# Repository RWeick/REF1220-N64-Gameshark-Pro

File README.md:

# REF1220-N64-Gameshark-Pro
An optimized PCB for the N64 Gameshark Pro as well as the full schematic. This is the second revision of the N64 Gameshark which was intended to support a smart card method of updating codes and adding features. The Gameshark Pro bin file should be programmed with the low bytes to the bottom SST and the high bytes to the top SST. It's worth noting that no smart cards were ever released for use with this Gameshark.

PCB Thickness: 1.2 mm

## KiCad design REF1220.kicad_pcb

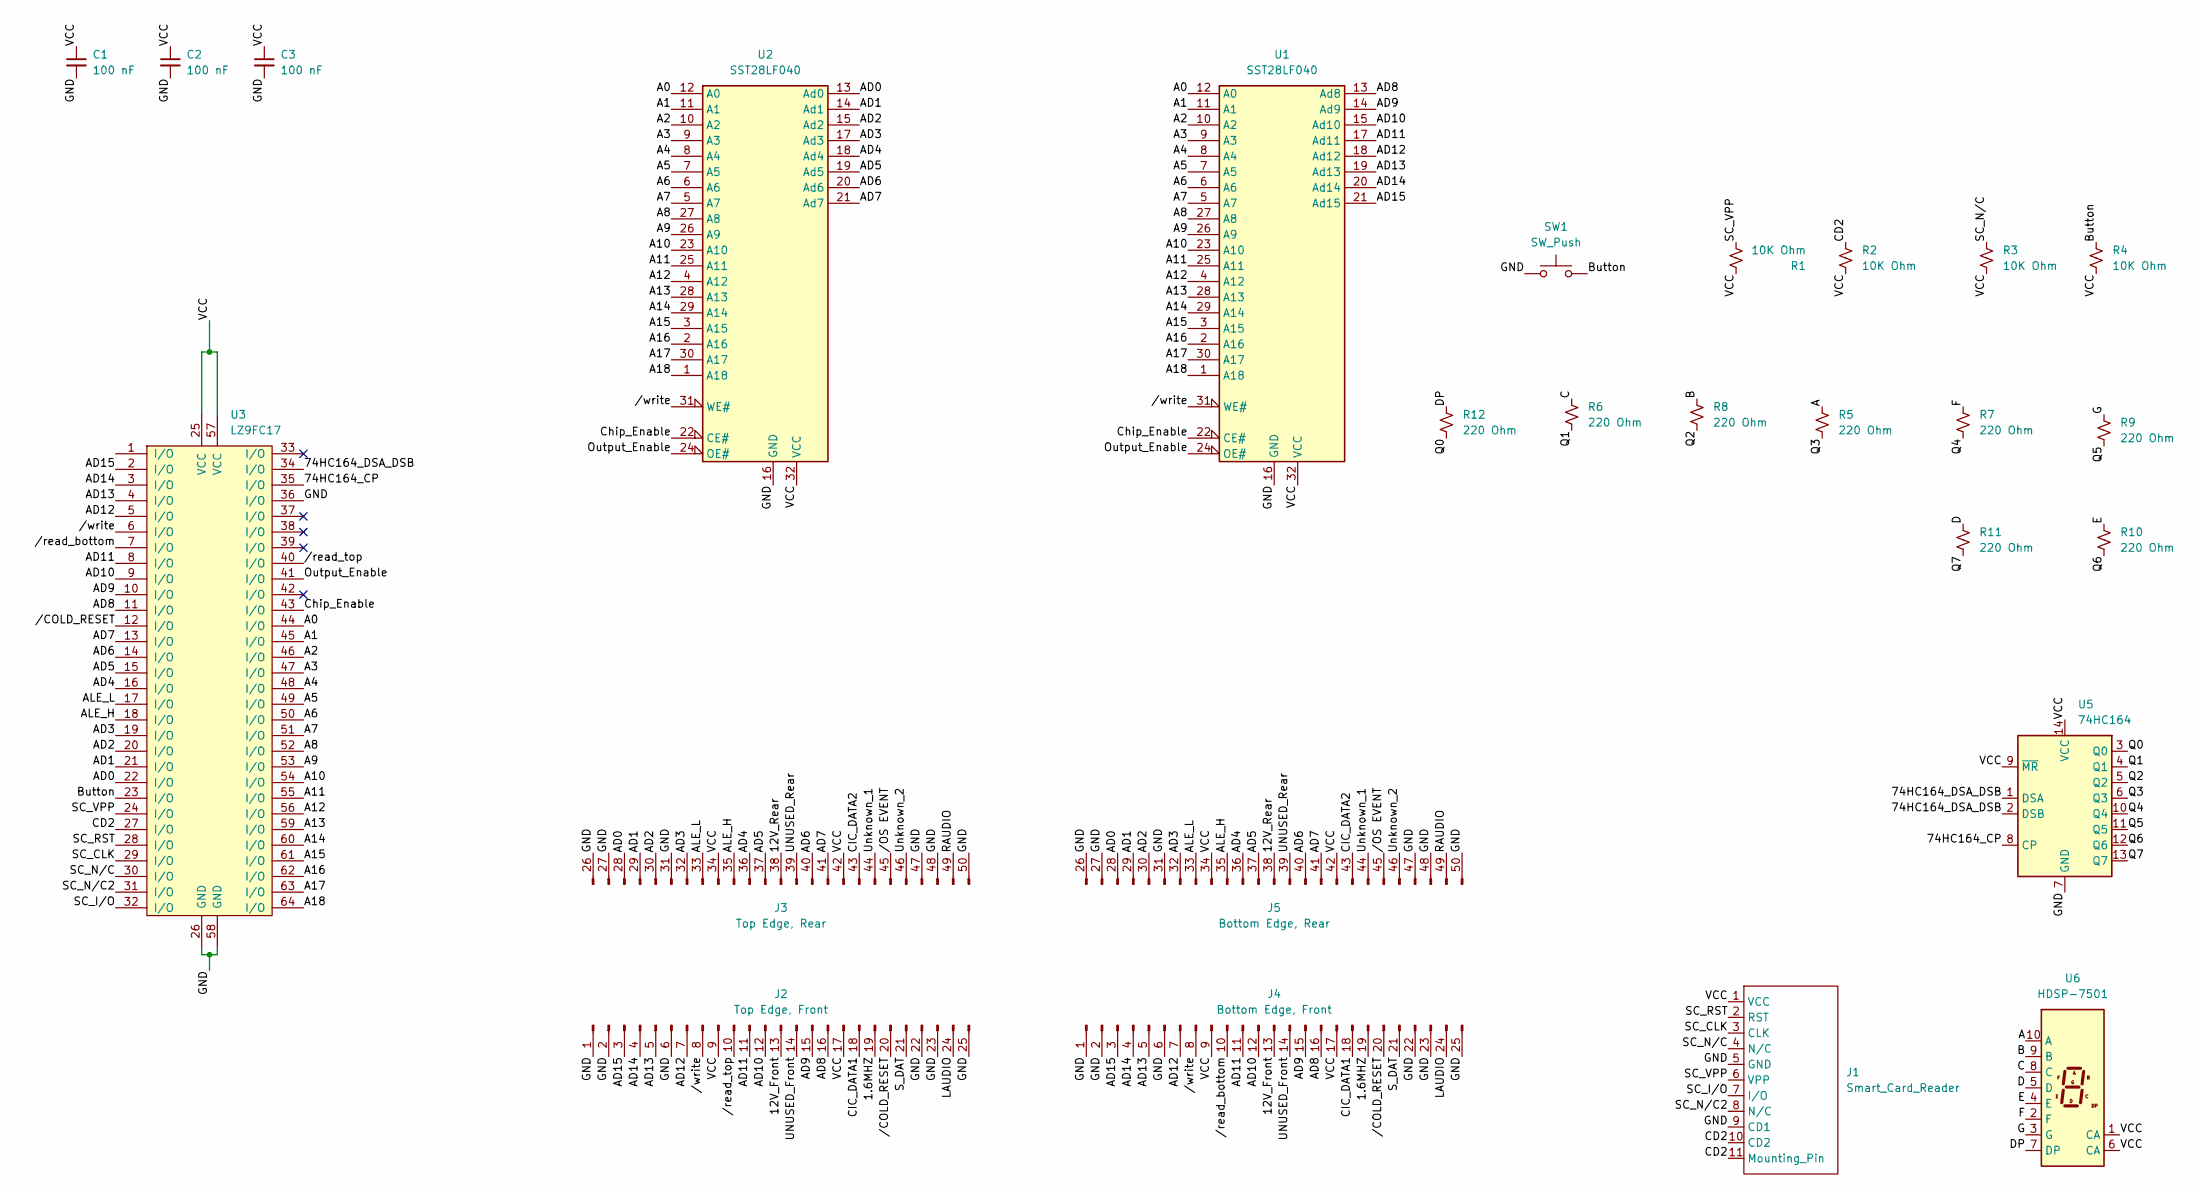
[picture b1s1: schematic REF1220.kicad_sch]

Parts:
C1, C2, C3: 100 nF; 100 nF Cap
J1: Smart_Card_Reader; Smart Card
J2: Top Edge, Front; Cart Edge Connector
J3: Top Edge, Rear; Cart Edge Connector Back
J4: Bottom Edge, Front; Cart Edge Connector
J5: Bottom Edge, Rear; Cart Edge Connector Back
R1, R2, R3, R4: 10K Ohm; 10k Ohm Resistor
R5, R6, R7, R8, R9, R10, R11, R12: 220 Ohm; 220 Ohm Resistor
SW1: SW_Push; 1mm Push Button
U1, U2: SST28LF040; PLCC32
U3: LZ9FC17; LZ9FC17 GAL
U5: 74HC164
U6: HDSP-7501; HDSP-7401

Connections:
/1.6MHZ: J2.19, J4.19
/12V_Front: J2.13, J4.13
/12V_Rear: J3.38 (Pin_13), J5.38 (Pin_13)
/74HC164_CP: U3.35 (I/O), U5.8 (CP)
/74HC164_DSA_DSB: U3.34 (I/O), U5.1 (DSA), U5.2 (DSB)
/A: R5.1, U6.10 (A)
/A0: U1.12 (A0), U2.12 (A0), U3.44 (I/O)
/A1: U1.11 (A1), U2.11 (A1), U3.45 (I/O)
/A2: U1.10 (A2), U2.10 (A2), U3.46 (I/O)
/A3: U1.9 (A3), U2.9 (A3), U3.47 (I/O)
/A4: U1.8 (A4), U2.8 (A4), U3.48 (I/O)
/A5: U1.7 (A5), U2.7 (A5), U3.49 (I/O)
/A6: U1.6 (A6), U2.6 (A6), U3.50 (I/O)
/A7: U1.5 (A7), U2.5 (A7), U3.51 (I/O)
/A8: U1.27 (A8), U2.27 (A8), U3.52 (I/O)
/A9: U1.26 (A9), U2.26 (A9), U3.53 (I/O)
/A10: U1.23 (A10), U2.23 (A10), U3.54 (I/O)
/A11: U1.25 (A11), U2.25 (A11), U3.55 (I/O)
/A12: U1.4 (A12), U2.4 (A12), U3.56 (I/O)
/A13: U1.28 (A13), U2.28 (A13), U3.59 (I/O)
/A14: U1.29 (A14), U2.29 (A14), U3.60 (I/O)
/A15: U1.3 (A15), U2.3 (A15), U3.61 (I/O)
/A16: U1.2 (A16), U2.2 (A16), U3.62 (I/O)
/A17: U1.30 (A17), U2.30 (A17), U3.63 (I/O)
/A18: U1.1 (A18), U2.1 (A18), U3.64 (I/O)
/AD0: J3.28 (Pin_3), J5.28 (Pin_23), U2.13 (Ad0), U3.22 (I/O)
/AD1: J3.29 (Pin_4), J5.29 (Pin_22), U2.14 (Ad1), U3.21 (I/O)
/AD2: J3.30 (Pin_5), J5.30 (Pin_21), U2.15 (Ad2), U3.20 (I/O)
/AD3: J3.32 (Pin_7), J5.32 (Pin_19), U2.17 (Ad3), U3.19 (I/O)
/AD4: J3.36 (Pin_11), J5.36 (Pin_15), U2.18 (Ad4), U3.16 (I/O)
/AD5: J3.37 (Pin_12), J5.37 (Pin_14), U2.19 (Ad5), U3.15 (I/O)
/AD6: J3.40 (Pin_15), J5.40 (Pin_11), U2.20 (Ad6), U3.14 (I/O)
/AD7: J3.41 (Pin_16), J5.41 (Pin_10), U2.21 (Ad7), U3.13 (I/O)
/AD8: J2.16, J4.16, U1.13 (Ad8), U3.11 (I/O)
/AD9: J2.15, J4.15, U1.14 (Ad9), U3.10 (I/O)
/AD10: J2.12, J4.12, U1.15 (Ad10), U3.9 (I/O)
/AD11: J2.11, J4.11, U1.17 (Ad11), U3.8 (I/O)
/AD12: J2.7, J4.7, U1.18 (Ad12), U3.5 (I/O)
/AD13: J2.5, J4.5, U1.19 (Ad13), U3.4 (I/O)
/AD14: J2.4, J4.4, U1.20 (Ad14), U3.3 (I/O)
/AD15: J2.3, J4.3, U1.21 (Ad15), U3.2 (I/O)
/ALE_H: J3.35 (Pin_10), J5.35 (Pin_16), U3.18 (I/O)
/ALE_L: J3.33 (Pin_8), J5.33 (Pin_18), U3.17 (I/O)
/B: R8.1, U6.9 (B)
/Button: R4.1, SW1.2, U3.23 (I/O)
/C: R6.1, U6.8 (C)
/CD2: J1.10 (CD2), J1.11 (Mounting_Pin), R2.1, U3.27 (I/O)
/CIC_DATA1: J2.18, J4.18
/CIC_DATA2: J3.43 (Pin_18), J5.43 (Pin_8)
/Chip_Enable: U1.22 (CE#), U2.22 (CE#), U3.43 (I/O)
/D: R11.1, U6.5 (D)
/DP: R12.1, U6.7 (DP)
/E: R10.1, U6.4 (E)
/F: R7.1, U6.2 (F)
/G: R9.1, U6.3 (G)
/GND: C1.2, C2.2, C3.2, J1.5 (GND), J1.9 (CD1), J2.1, J2.2, J2.6, J2.22, J2.23, J2.25, J3.26 (Pin_1), J3.27 (Pin_2), J3.31 (Pin_6), J3.47 (Pin_22), J3.48 (Pin_23), J3.50 (Pin_25), J4.1, J4.2, J4.6, J4.22, J4.23, J4.25, J5.26 (Pin_25), J5.27 (Pin_24), J5.31 (Pin_20), J5.47 (Pin_4), J5.48 (Pin_3), J5.50 (Pin_1), SW1.1, U1.16 (GND), U2.16 (GND), U3.26 (GND), U3.36 (I/O), U3.58 (GND), U5.7 (GND)
/LAUDIO: J2.24, J4.24
/Output_Enable: U1.24 (OE#), U2.24 (OE#), U3.41 (I/O)
/Q0: R12.2, U5.3 (Q0)
/Q1: R6.2, U5.4 (Q1)
/Q2: R8.2, U5.5 (Q2)
/Q3: R5.2, U5.6 (Q3)
/Q4: R7.2, U5.10 (Q4)
/Q5: R9.2, U5.11 (Q5)
/Q6: R10.2, U5.12 (Q6)
/Q7: R11.2, U5.13 (Q7)
/RAUDIO: J3.49 (Pin_24), J5.49 (Pin_2)
/SC_CLK: J1.3 (CLK), U3.29 (I/O)
/SC_I/O: J1.7 (I/O), U3.32 (I/O)
/SC_N/C: J1.4 (N/C), R3.1, U3.30 (I/O)
/SC_N/C2: J1.8 (N/C), U3.31 (I/O)
/SC_RST: J1.2 (RST), U3.28 (I/O)
/SC_VPP: J1.6 (VPP), R1.1, U3.24 (I/O)
/S_DAT: J2.21, J4.21
/UNUSED_Front: J2.14, J4.14
/UNUSED_Rear: J3.39 (Pin_14), J5.39 (Pin_12)
/Unknown_1: J3.44 (Pin_19), J5.44 (Pin_7)
/Unknown_2: J3.46 (Pin_21), J5.46 (Pin_5)
/VCC: C1.1, C2.1, C3.1, J1.1 (VCC), J2.9, J2.17, J3.34 (Pin_9), J3.42 (Pin_17), J4.9, J4.17, J5.34 (Pin_17), J5.42 (Pin_9), R1.2, R2.2, R3.2, R4.2, U1.32 (VCC), U2.32 (VCC), U3.25 (VCC), U3.57 (VCC), U5.9 (~MR), U5.14 (VCC), U6.1 (CA), U6.6 (CA)
//COLD_RESET: J2.20, J4.20, U3.12 (I/O)
//OS EVENT: J3.45 (Pin_20), J5.45 (Pin_6)
//read_bottom: J4.10, U3.7 (I/O)
//read_top: J2.10, U3.40 (I/O)
//write: J2.8, J4.8, U1.31 (WE#), U2.31 (WE#), U3.6 (I/O)

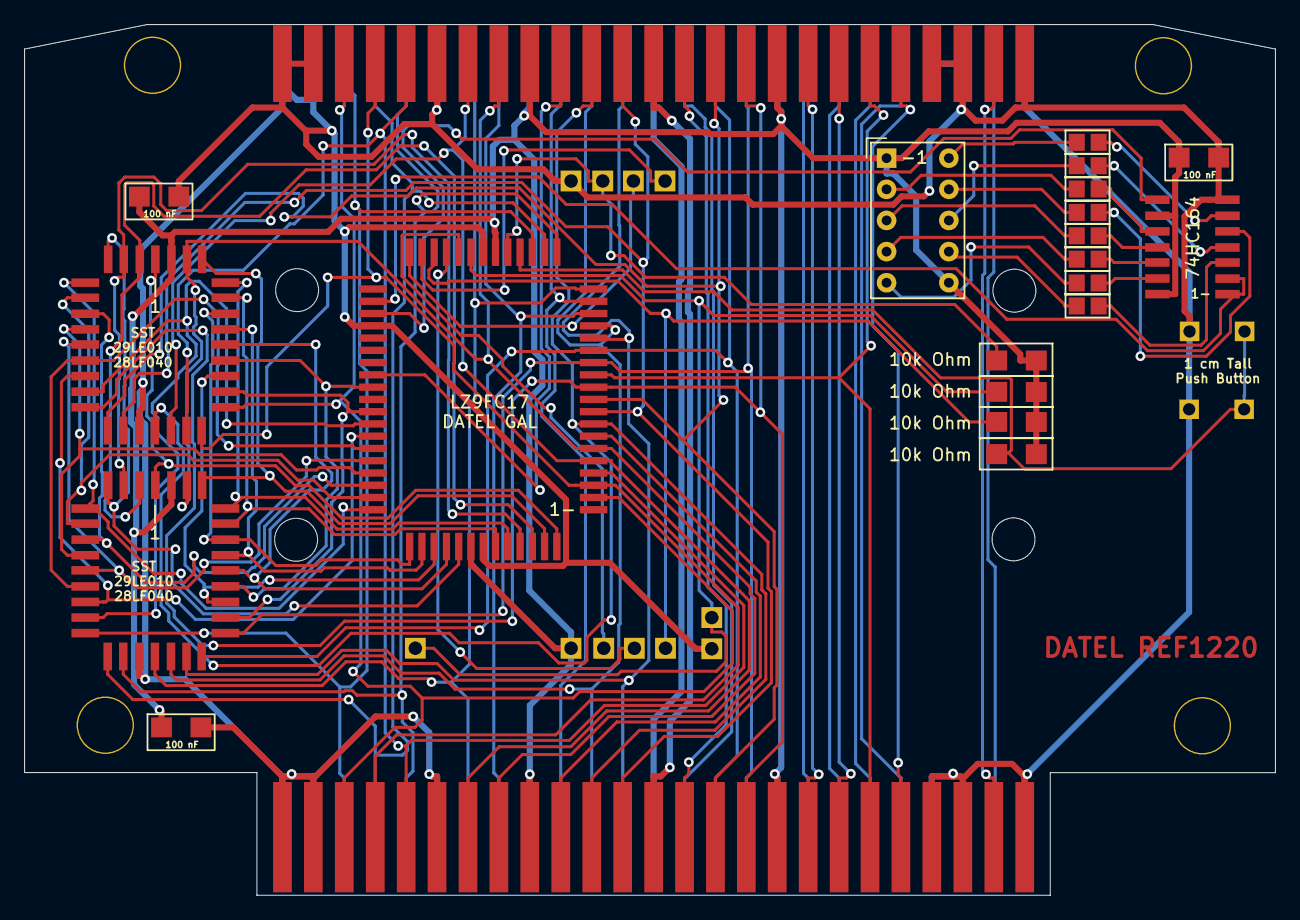
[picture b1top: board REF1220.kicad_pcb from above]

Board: 2 copper layers, 102.0 x 71.0 mm, 34 parts (0 on the bottom side), 84 nets.

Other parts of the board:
Hole1, Hole2, Hole3, Hole4: N64-Hole
Hole5, Hole6, Hole7, Hole8: MountingHole_2.1mm
